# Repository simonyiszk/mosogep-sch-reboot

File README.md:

# mosogep-sch-reboot
Mosogep.sch project reboot

Projekt dokumentáció: https://docs.google.com/document/d/1uoIA5JC5i7Pd-E8AlqeZ2zfmS9e4bSQlHUPqoVc_8NE/edit?tab=t.0

Mappaszerkezet:
- HW: a boardok tervrajzai
- FW: boardon futó firmware
- scripts: random scriptek amiket használtunk
- backend: itt van a backend kód
- frontend: itt van a frontend kód
- proxy: a proxy konfigurációja
- collector: a szerveroldali adatgyűjtés kódja

Az előtúrt fileokat eredeti formájukban az "eredeti" branchon találod.

Build & launch
- `git pull --recurse-submodules git@github.com:simonyiszk/mosogep-sch-reboot.git` VAGY `git submodule init && git submodule update` pull után
- `cp .env.dist .env`
- `.env`-ben ki kell tölteni a `BACKEND_SECRET_KEY`-t valami titkosra, illetve célszerű `ALLOWED_HOSTS`-ot localhosnak megfelelőre
- `docker-compose up`
- InfluxDB beállítás `localhost:8086`-on, bucket name célszerűen `statusch`, vagy `.env`-ben be kell állítani!
  Jó az elején kapott, minden joggal rendelkező token is (dev célra), vagy generáljunk a buckethez egy read/write tokent, és használjuk azt
- a `docker-compose`-t a `Ctrl+C`-vel megállít, majd újraindít (ismert hiba 'ContainerConfig', ekkor `docker-compose down` és utána up)

A backend a `8000`-es, a frontend a `3000`-es, az influx a `8086`-os porton fut. A `proxy` mappa Caddy konfigja kiproxyzza a frontendet és a backend API-t, ami dockerből automatikusan indul. Production-ben a Caddyfile-t át kell írni a megfelelő hostra.

Dev célra a leghasznosabb script a `scripts/fake_sender`, ami kamu adatokat küld az influxdb-be.

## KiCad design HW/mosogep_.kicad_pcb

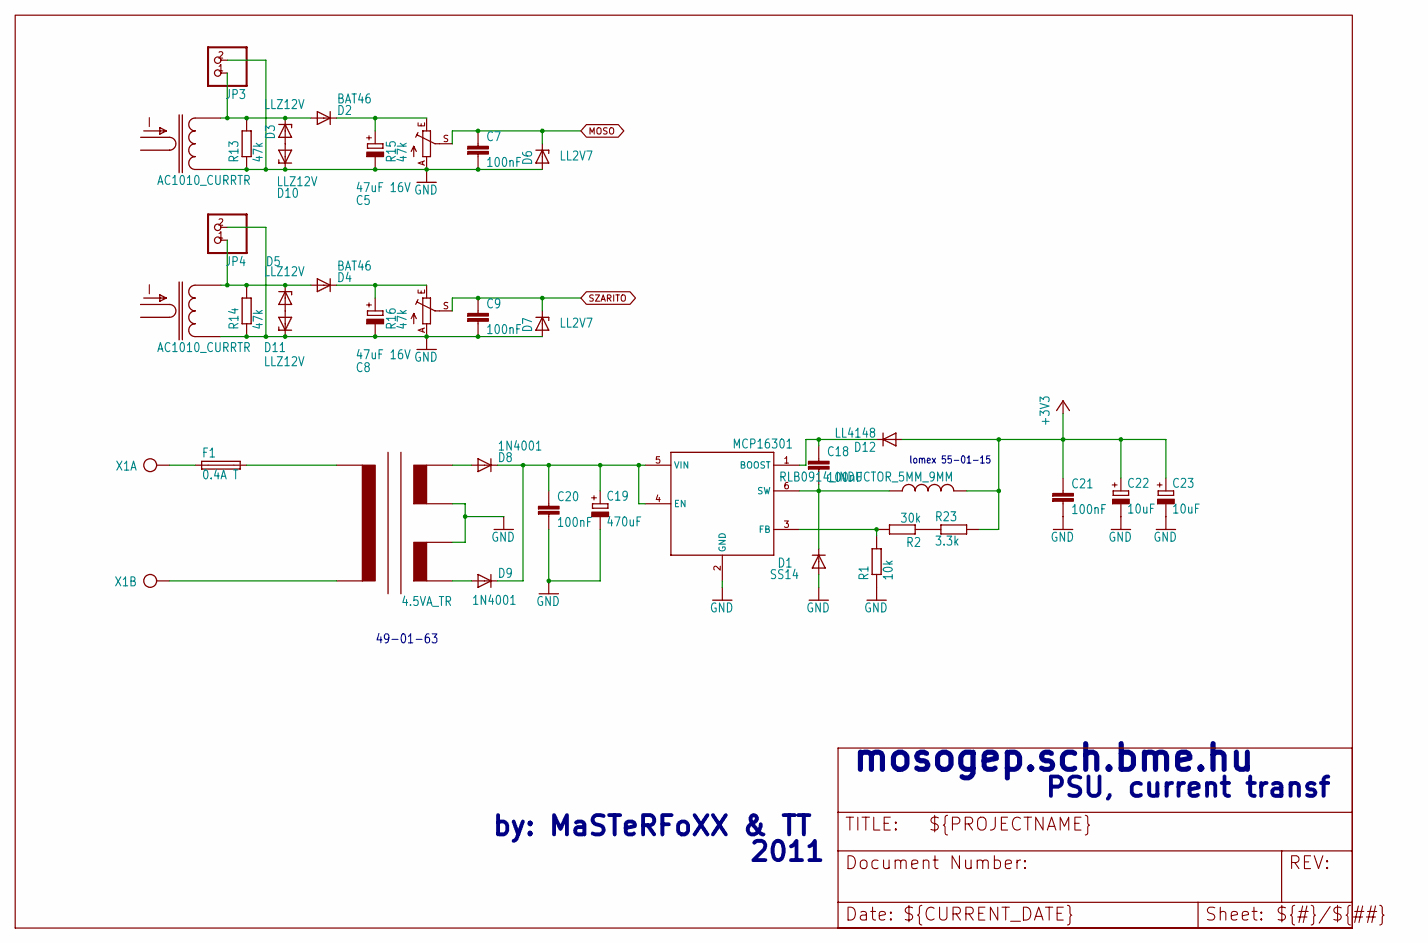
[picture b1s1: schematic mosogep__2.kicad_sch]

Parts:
C5, C8: 47uF 16V; E2,5-5
C7, C9, C18, C20, C21: 100nF; C1206K
C19: 470uF; E5-10,5
C22, C23: 10uF; B_3528-21R
D1: SS14; DO-214AC
D2, D4: BAT46; SOD80C
D3, D5, D10, D11: LLZ12V; SOD80C
D6, D7: LL2V7; SOD80C
D8, D9: 1N4001; D-7.5
D12: LL4148; SOD80C
F1: 0.4A T; SH22,5A
IC2: MCP16301; SOT23-6
JP3, JP4: PINHD-1X2; 1X02
L3: RLB0914_INDUCTOR_5MM_9MM; L_5MM
R1: 10k; R1206
R2: 30k; R1206
R13, R14: 47k; M1206
R15, R16: 47k; RJ9W
R23: 3.3k; R1206
TR1: 4.5VA_TR; TR4.5VA
TR1_MOSOGEP0, TR2_SZARITO0: AC1010_CURRTR; CURRTR_TALEMA
X1: AK500/2; AK500_2

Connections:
+3V3: C21.1, C22.+, C23.+, D12.A, L3.P$2 (2), R23.2; also elsewhere on the board
GND: C5.-, C7.2, C8.-, C9.2, C19.-, C20.2, C21.2, C22.-, C23.-, D1.A, D6.A, D7.A, D10.C, D11.C, IC2.2 (GND), JP3.2, JP4.2, R1.1, R13.1, R14.1, R15.A, R16.A, TR1.SA_2, TR1.SB1 (SB_1), TR1_MOSOGEP0.2, TR2_SZARITO0.2; also elsewhere on the board
MOSO: C7.1, D6.C, R15.S; also elsewhere on the board
unnamed: D4.A, D5.C, JP4.1, R14.2, TR2_SZARITO0.1
unnamed: C18.2, D1.C, IC2.6 (SW), L3.P$1 (1)
unnamed: D2.A, D3.C, JP3.1, R13.2, TR1_MOSOGEP0.1
unnamed: C18.1, D12.C, IC2.1 (BOOST)
unnamed: C5.+, D2.C, R15.E
unnamed: D3.A, D10.A
unnamed: R2.1, R23.1
unnamed: F1.1, X1.1
unnamed: C8.+, D4.C, R16.E
unnamed: TR1.PR2 (PRI2), X1.2
unnamed: F1.2, TR1.PR1 (PRI1)
unnamed: D8.A, TR1.SA_1
unnamed: D9.A, TR1.SB2 (SB_2)
unnamed: D5.A, D11.A
unnamed: C19.+, C20.1, D8.C, D9.C, IC2.4 (EN), IC2.5 (VIN)
SZARITO: C9.1, D7.C, R16.S; also elsewhere on the board
VREF: IC2.3 (FB), R1.2, R2.2

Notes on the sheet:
mosogep.sch.bme.hu
lomex 55-01-15
PSU, current transf
by: MaSTeRFoXX & TT
2011
49-01-63

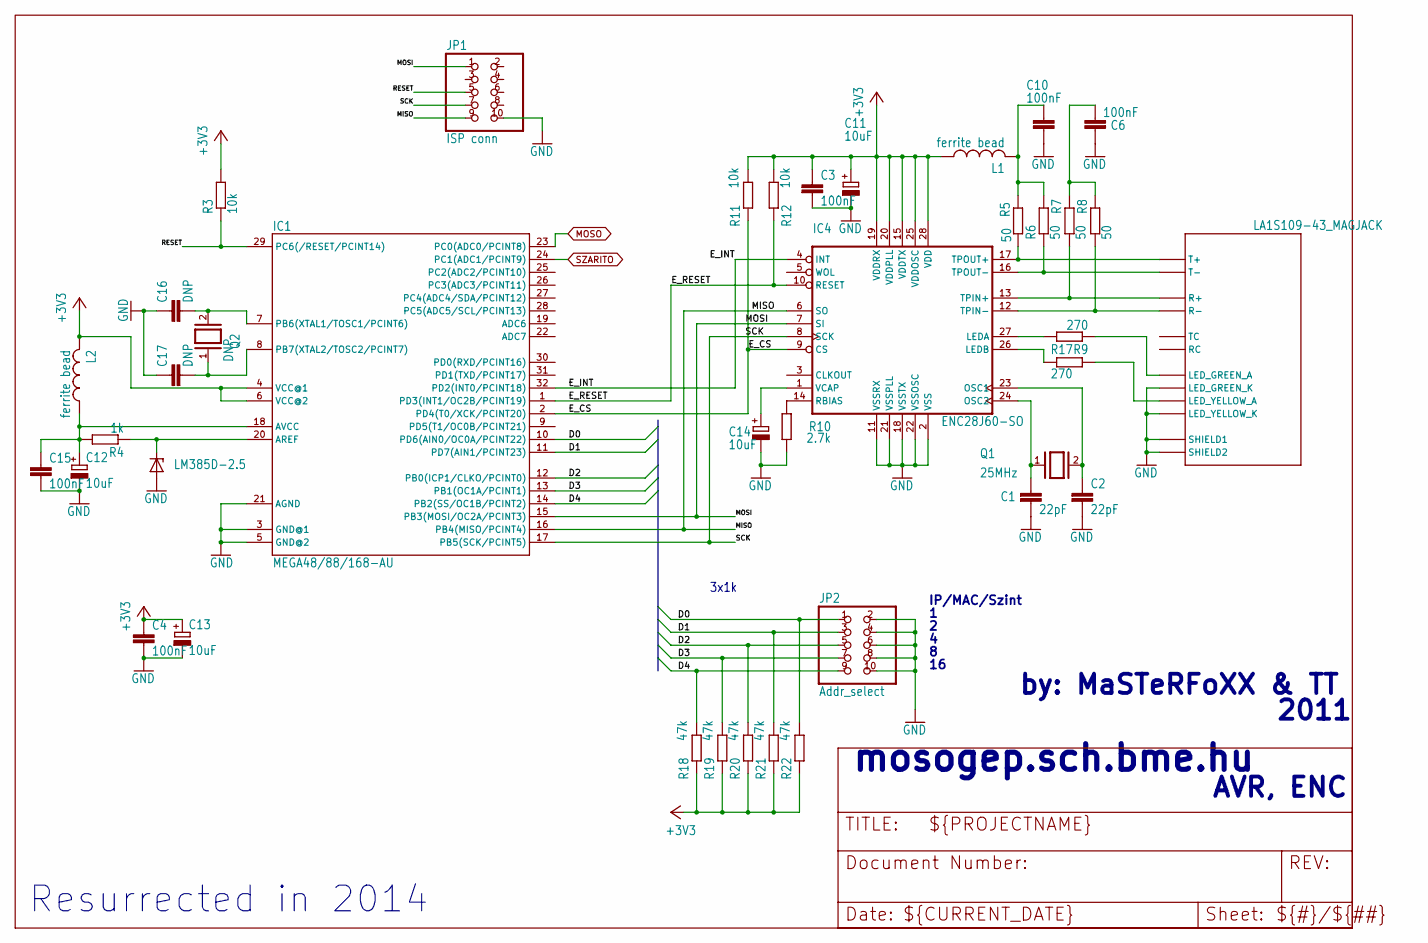
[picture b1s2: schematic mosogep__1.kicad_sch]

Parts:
C1, C2: 22pF; C1206K
C3, C4, C6, C10, C15: 100nF; C1206K
C11, C12, C13, C14: 10uF; B_3528-21R
C16, C17: DNP; C1206K
CN1: LA1S109-43_MAGJACK; LA1S109_MAGJACK
IC1: MEGA48/88/168-AU; TQFP32-08
IC3: LM385D-2.5; SO08
IC4: ENC28J60-SO; SO28W
JP1: ISP conn; 2X05
JP2: Addr_select; 2X05
L1, L2: ferrite bead; L3225M
Q1: 25MHz; QS
Q2: DNP; QS
R3, R11, R12: 10k; M1206
R4: 1k; M1206
R5, R6, R7, R8: 50; M1206
R9, R17: 270; M1206
R10: 2.7k; M1206
R18, R19, R20, R21, R22: 47k; M1206

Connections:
+3V3: C3.1, C4.1, C11.+, C13.+, IC1.4 (VCC@1), IC1.6 (VCC@2), IC4.15 (VDDTX), IC4.19 (VDDRX), IC4.20 (VDDPLL), IC4.25 (VDDOSC), IC4.28 (VDD), L1.1, L2.2, R3.2, R11.2, R12.2, R18.1, R19.1, R20.1, R21.1, R22.1; also elsewhere on the board
AREF: IC1.20 (AREF), IC3.8 (C), R4.1
D0: IC1.10 (PD6(AIN0/OC0A/PCINT22)), JP2.1, R22.2
D1: IC1.11 (PD7(AIN1/PCINT23)), JP2.3, R21.2
D2: IC1.12 (PB0(ICP1/CLKO/PCINT0)), JP2.5, R20.2
D3: IC1.13 (PB1(OC1A/PCINT1)), JP2.7, R19.2
D4: IC1.14 (PB2(SS/OC1B/PCINT2)), JP2.9, R18.2
E_CS: IC1.2 (PD4(T0/XCK/PCINT20)), IC4.9 (CS), R11.1
E_INT: IC1.32 (PD2(INT0/PCINT18)), IC4.4 (INT)
E_RESET: IC1.1 (PD3(INT1/OC2B/PCINT19)), IC4.10 (RESET), R12.1
GND: C1.2, C2.2, C3.2, C4.2, C6.1, C10.2, C11.-, C12.-, C13.-, C14.-, C15.2, C16.1, C17.1, CN1.GREEN- (LED_GREEN_K), CN1.SHIELD (SHIELD1), CN1.SHIELD2, CN1.YELLOW- (LED_YELLOW_K), IC1.3 (GND@1), IC1.5 (GND@2), IC1.21 (AGND), IC3.4 (A), IC4.2 (VSS), IC4.11 (VSSRX), IC4.18 (VSSTX), IC4.21 (VSSPLL), IC4.22 (VSSOSC), JP1.10, JP2.2, JP2.4, JP2.6, JP2.8, JP2.10, R10.1; also elsewhere on the board
MISO: IC1.16 (PB4(MISO/PCINT4)), IC4.6 (SO), JP1.9
MOSI: IC1.15 (PB3(MOSI/OC2A/PCINT3)), IC4.7 (SI), JP1.1
MOSO: IC1.23 (PC0(ADC0/PCINT8)); also elsewhere on the board
unnamed: IC4.27 (LEDA), R9.2
unnamed: C12.+, C15.1, IC1.18 (AVCC), L2.1, R4.2
unnamed: C1.1, IC4.24 (OSC2), Q1.1
unnamed: C2.1, IC4.23 (OSC1), Q1.2
unnamed: CN1.P$1 (T+), IC4.17 (TPOUT+), R5.2
unnamed: CN1.P$2 (T-), IC4.16 (TPOUT-), R6.1
unnamed: CN1.P$3 (R+), IC4.13 (TPIN+), R7.1
unnamed: CN1.P$4 (R-), IC4.12 (TPIN-), R8.1
unnamed: C10.1, L1.2, R5.1, R6.2
unnamed: C6.2, R7.2, R8.2
unnamed: IC4.14 (RBIAS), R10.2
unnamed: C14.+, IC4.1 (VCAP)
unnamed: CN1.GREEN+ (LED_GREEN_A), R9.1
unnamed: CN1.YELLO+ (LED_YELLOW_A), R17.2
unnamed: IC4.26 (LEDB), R17.1
unnamed: C16.2, IC1.7 (PB6(XTAL1/TOSC1/PCINT6)), Q2.2
unnamed: C17.2, IC1.8 (PB7(XTAL2/TOSC2/PCINT7)), Q2.1
RESET: IC1.29 (PC6(/RESET/PCINT14)), JP1.5, R3.1
SCK: IC1.17 (PB5(SCK/PCINT5)), IC4.8 (SCK), JP1.7
SZARITO: IC1.24 (PC1(ADC1/PCINT9)); also elsewhere on the board

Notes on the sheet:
by: MaSTeRFoXX & TT
3x1k
2011
AVR, ENC
mosogep.sch.bme.hu
Resurrected in 2014~{}
IP/MAC/Szint

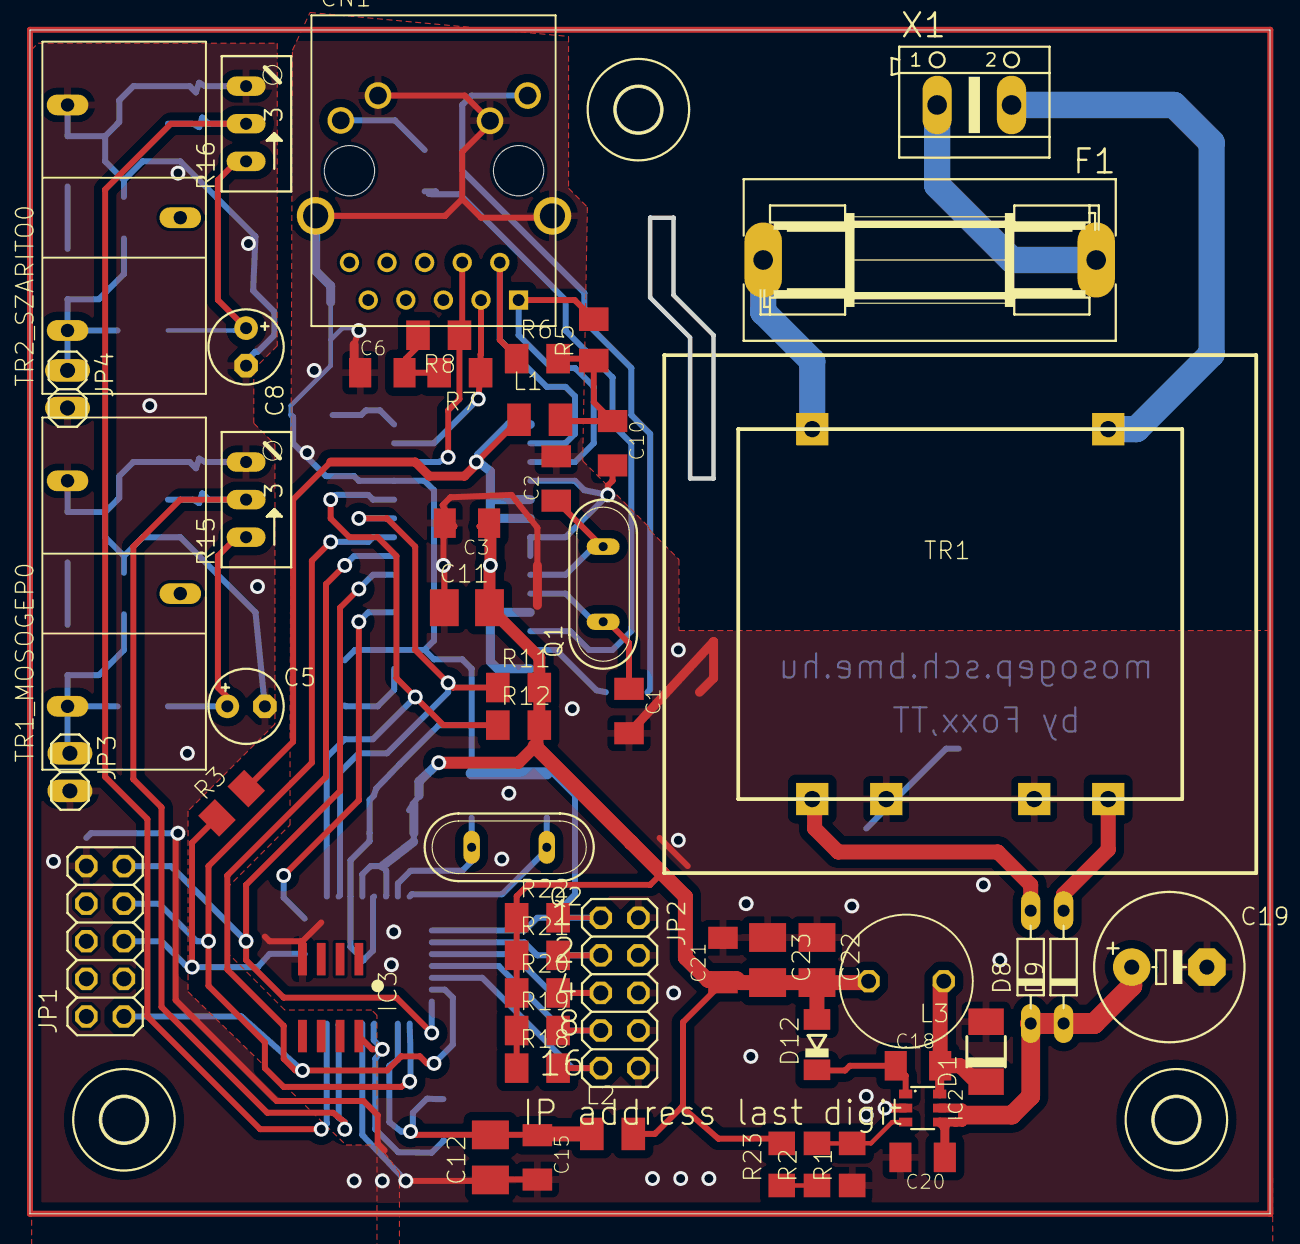
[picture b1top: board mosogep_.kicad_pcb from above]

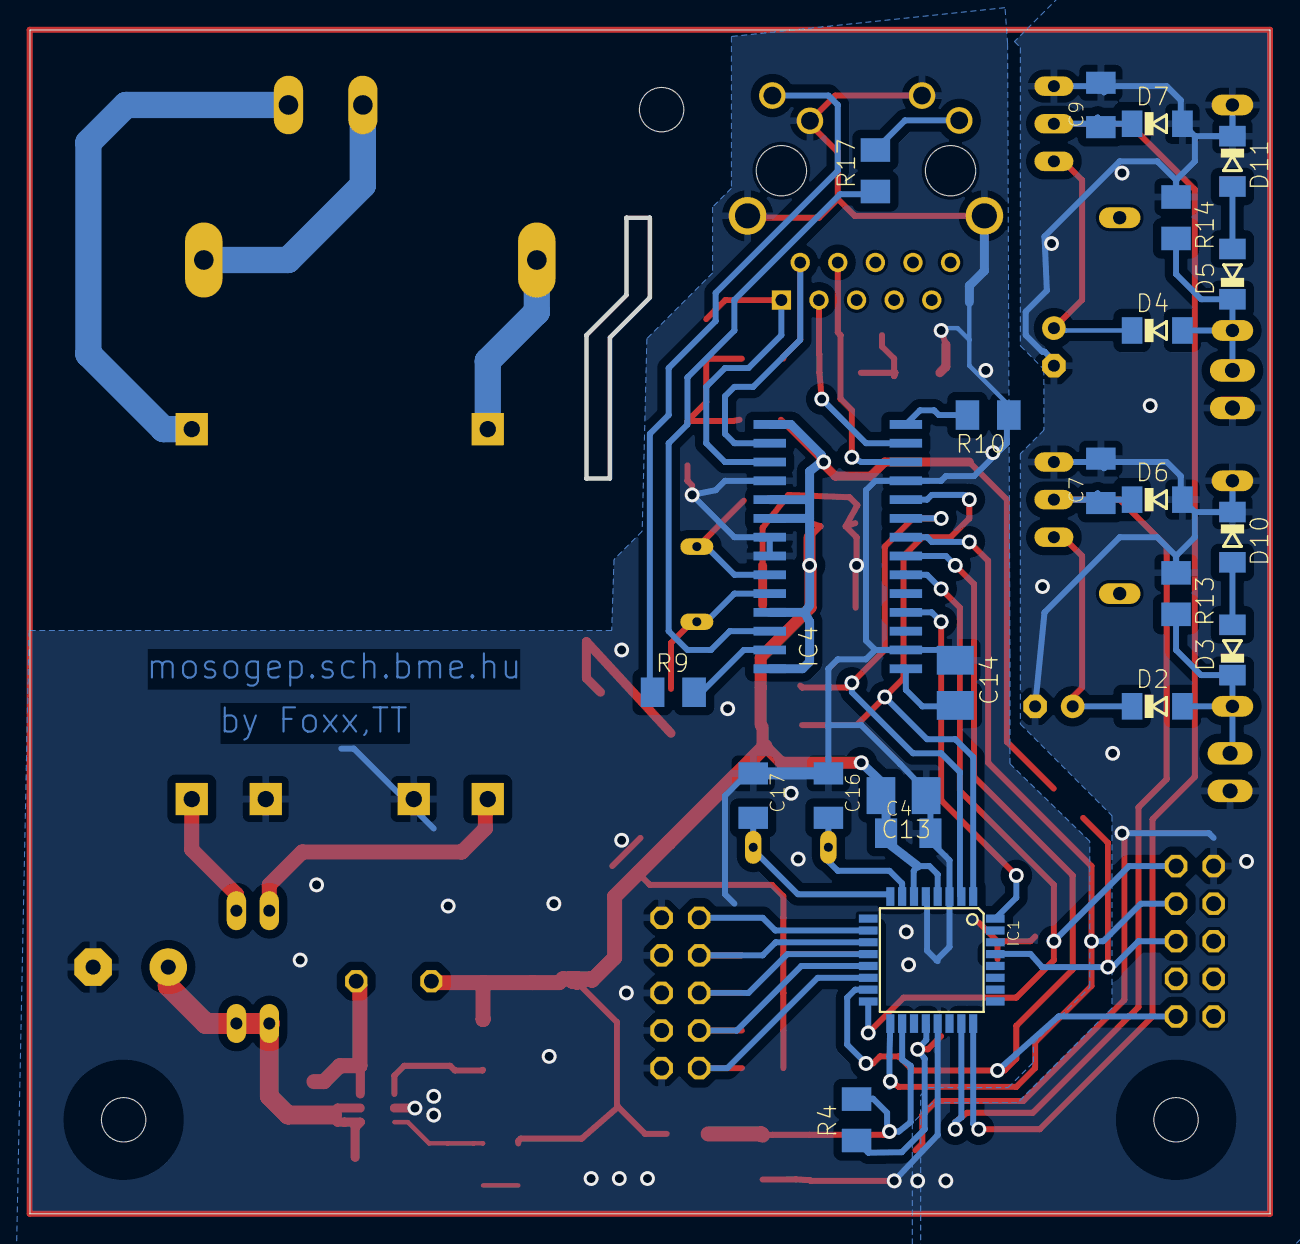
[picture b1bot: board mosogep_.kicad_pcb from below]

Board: 2 copper layers, 83.5 x 79.7 mm, 80 parts (23 on the bottom side), 50 nets.

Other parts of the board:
U$1, U$2, U$4: 3,0

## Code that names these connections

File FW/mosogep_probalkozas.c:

/*
 * main.c
 *
 *  Created on: 2014.03.25.
 *      Author: MaSTeRFoXX
 */

#ifdef DEBUG
#include "uart.h"
#else
#define printf(...)
#endif
#include "enc28j60.h"
#include "ip_arp_udp_tcp.h"
#include <avr/io.h>
#include <avr/wdt.h>
#include <stdio.h>
#include <util/delay.h>


FUSES = 
{
    // 0x62, or
    // internal RC oscillator at 8MHz, divided by 8
    .low = LFUSE_DEFAULT,

    // 0xDF
    // - BOD disabled
    // - EESAVE off
    // - RESET enabled
    // - ISP/SPI enabled
    // - DebugWire off
    // - Watchdog not forced
    .high = HFUSE_DEFAULT,

    // default value
    .extended = EFUSE_DEFAULT,
};



#define ENC_RESET PD3

// webszerver demo kod alapjan teszt celbol
static uint8_t mymac[6] = {0x54, 0x55, 0x58, 0x10, 0x00, 0x29};
static uint8_t myip[4] = {192, 168, 2, 5}; // aka http://10.0.0.29/
uint8_t allxff[6] = {
    0xff, 0xff, 0xff, 0xff,
    0xff, 0xff}; // all of it can be used as mac, the first 4 can be used as IP
// server listen port for www
#define MYWWWPORT 80

// frame format
//[IP0][IP1][IP2][IP3]

// global packet buffer
#define BUFFER_SIZE 550
static uint8_t buf[BUFFER_SIZE + 1];

volatile uint8_t moso_H;
volatile uint8_t moso_L;
volatile uint8_t szarito_H;
volatile uint8_t szarito_L;

// GPIO meg egyeb HW beallitasok
void hw_init() {
#ifdef DEBUG
  // for printf
  usart_initialize();
  stdout = &uart_output;

  // for debug LED
  DDRC |= (1 << PC2);
  PORTC |= (1 << PC2);
#endif
  // DDRC|=(1<<PC0);
  DDRD |= (1 << ENC_RESET);
  PORTD &= ~(1 << ENC_RESET);
  _delay_ms(1000); // ENC28J60 RESET pulse
  PORTD |= (1 << ENC_RESET);

  DDRB = (1 << PB2);
  // ADC init
  ADCSRA |= (1 << ADEN) | (1 << ADPS2) | (1 << ADPS1); // clk/64 az ADC clock
  // Digital input disable, nemtom kell-e de nem baj ha van
  // DIDR0 |=(1<<ADC0D) | (1<<ADC1D);  wat nem ismeri a regisztert
}

// beolvassa a jumperok allasat, ez adja az IP CIM veget, a MAC c�m veget
// ez benne is lesz a csomag elejen
uint8_t read_jumpers(void) {
  // Mivel PB2 = /SS, ha input és low az megbassza az SPI-t
  // ezt meg lehet kerülni, ha outputnak használjuk, és csak a beolvasás idejére
  // kapcsoljuk inputba

  DDRB &= ~(1 << PB2);

  uint8_t temp = 0;
  if (!(PIND & (1 << PD6)))
    temp |= 1;
  if (!(PIND & (1 << PD7)))
    temp |= 2;
  if (!(PINB & (1 << PB0)))
    temp |= 4;
  if (!(PINB & (1 << PB1)))
    temp |= 8;
  if (!(PINB & (1 << PB2)))
    temp |= 16;

  // PB2 visszakapcsolása
  // mivel lehet rajta jumper, ezért csak LOW state lehet
  PORTB &= ~(1 << PB2);
  DDRB |= (1 << PB2);

  // mivel így már minden szintet be lehet programozni, nem kell a 17-re
  // speciális elbánás
  if (temp == 0)
    temp = 99;
  return temp;
}

int main(void) {
  uint16_t dat_p;
  uint8_t dat[] =
      "          Mosogep.sch by SEM. SEM RULEZ! (FW by .:: FoXX::. 2014)!\0";

  _delay_ms(100);
  hw_init();
  printf("Begin init\n");
  //   wdt_enable(WDTO_1S);
  // szint c�m beolvasasa ennek megfeleloen all be a mac es IP cim
  myip[3] = read_jumpers();
  mymac[5] = read_jumpers();
  printf("Jumpers read: %d\n", myip[3]);

  printf("Start initing ENC28\n");
  // wdt_reset();
  // initialize the hardware driver for the enc28j60
  enc28j60Init(mymac);
  printf("ENC init done\n");

  _delay_loop_1(0); // 60us
  enc28j60PhyWrite(PHLCON, 0x476);
  // init the ethernet/ip layer:
  init_udp_or_www_server(mymac, myip);
  www_server_port(MYWWWPORT);
  printf("All init done\n");

  while (1) {
    //       wdt_reset();
#ifdef DEBUG
    PORTC ^= (1 << PC2);
#endif
    _delay_ms(100);
    // mosogep megmerese
    ADMUX = (ADMUX & 0xf0) | 0; // mosogep kivalasztasa
    _delay_ms(10);              // varni a SH kapacitasra
    ADCSRA |= (1 << ADSC);      // meres start
    while (!(ADCSRA & (1 << ADIF)))
      ;                    // var amig kesz nem lesz
    ADCSRA |= (1 << ADIF); // flag torlese, 1-es beirasavaol
    moso_L = ADCL;
    moso_H = ADCH;

    // szarito megmerese
    ADMUX = (ADMUX & 0xf0) | 1; // szarito kivalasztasa
    _delay_ms(10);              // varni a SH kapacitasra
    ADCSRA |= (1 << ADSC);      // meres start
    while (!(ADCSRA & (1 << ADIF)))
      ;                    // var amig kesz nem lesz
    ADCSRA |= (1 << ADIF); // flag torlese, 1-es beirasavaol
    szarito_L = ADCL;
    szarito_H = ADCH;

    // frame osszepakolasa
    dat[0] = myip[0]; // ip cim
    dat[1] = myip[1];
    dat[2] = myip[2];
    dat[3] = myip[3];
    dat[4] = moso_H;    // mosogep_H byte
    dat[5] = moso_L;    // mosogep_L byte
    dat[6] = szarito_H; // szaritogep_H byte
    dat[7] = szarito_L; // szaritogep_L byte
    printf("Got data: moso=%d szarito=%d\n", moso_H << 8 + moso_L,
           szarito_H << 8 + szarito_L);
    send_udp(buf, dat, sizeof(dat), 1234, allxff, 1234, allxff);
  }
  return (0);
}

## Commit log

2025-01-24 HW feltöltése
    Kicad konverzió by Turi Marci
2025-01-24 Exportált PDF-ek törlése
    Schematic hibás volt, a másik kettő nem jól használható
2025-01-24 Eredeti kód
2025-01-24 Driver fix: processzor órajel clash
    8 megára volt fixen állítva, pedig egyébként a kristály le van osztva
    A valódi órajel 1 mega, és amúgy is jobb ötlet a makefileban állítani.
2025-01-24 Add Makefile
2025-01-24 Fix deprecation warnings
    prog_char* -> PGM_P
2025-01-24 Add basic debugging over UART
    From https://github.com/ptrks/avr-usart-printf
2025-01-24 Fix uart build warnings
2025-01-24 Delay fixálása
    Nem használt busy wait loop törlése, stdlibes verzió haználata
2025-01-24 Jumper beolvasás javítása
    A PB2 = SPI SS láb hülyén viselkedik,
    ezért a korábbi paneleken ki volt kapcsolva,
    és a 16-os bitet nem lehetett állítani
    Ezt SW-ből fixáltam
2025-01-24 Update project metadata
2025-01-24 DEBUG LED átalakítása
    PC0-án nem volt led soha, PC2-re viszont könnyen felrakható egy
2025-01-24 Make debug optional
2025-01-24 Run formatter
2025-01-24 Add fuses and flashing them
2025-02-26 Upload scipts
2025-02-26 Upload PDF schematic
2025-02-27 Add backend as submodule
2025-02-28 Add frontend as submodule
2025-02-28 Update backend
2025-02-28 Updated submodule frontend
2025-02-28 Add proxy config and compose file
2025-02-28 Add collector
2025-02-28 Már van
2025-02-28 Update Caddyfile for development use
2025-02-28 Add fake sender script
2025-03-01 Update submodules
2025-03-15 Update README.md
    Dokumentáció linkelése
2025-04-05 Update frontend
